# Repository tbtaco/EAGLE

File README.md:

This repository is for any custom PCBs I make that aren't directly part of another project.

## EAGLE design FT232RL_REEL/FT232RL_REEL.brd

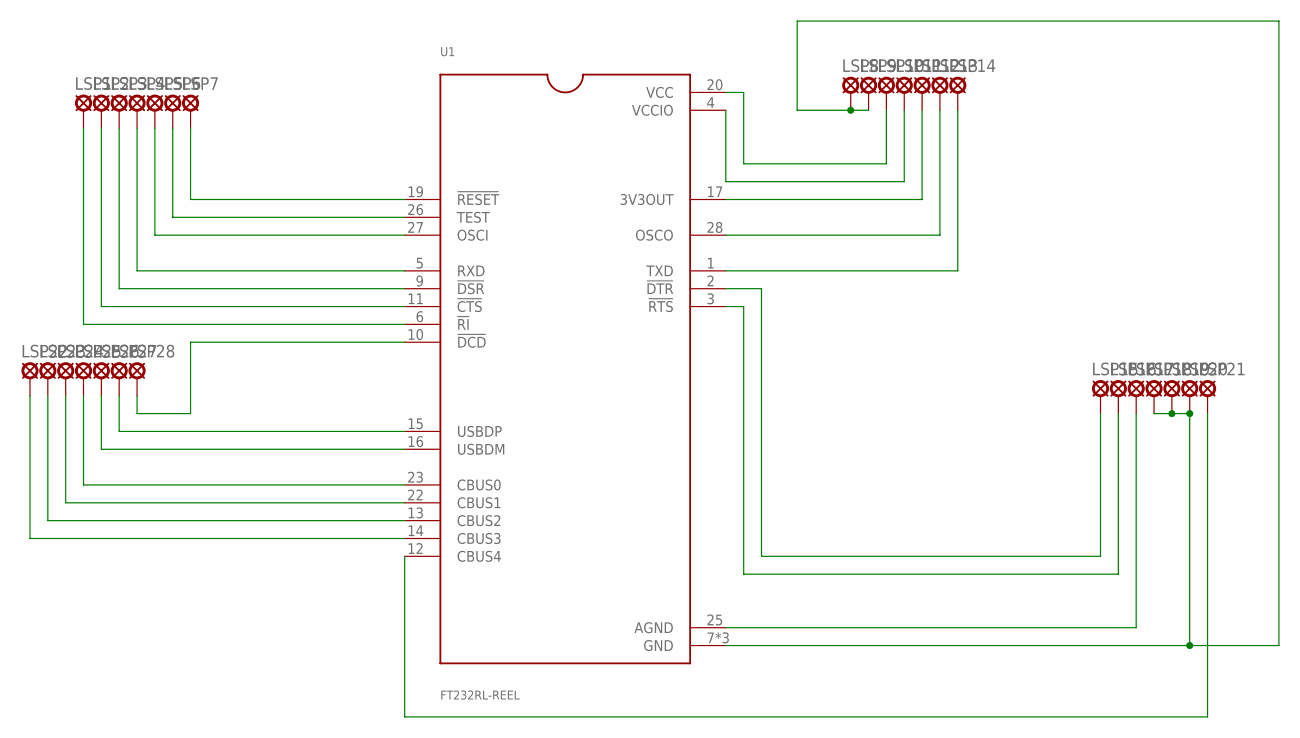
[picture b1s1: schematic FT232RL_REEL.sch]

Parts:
LSP1, LSP2, LSP3, LSP4, LSP5, LSP6, LSP7, LSP8, LSP9, LSP10, LSP11, LSP12, LSP13, LSP14, LSP15, LSP16, LSP17, LSP18, LSP19, LSP20, LSP21, LSP22, LSP23, LSP24, LSP25, LSP26, LSP27, LSP28: LSP10_CLSP10_C; LSP10_C
U1: FT232RL-REEL; SOP65P780X200-28N

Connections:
unnamed: LSP7.P$1, U1.19 (!RESET)
unnamed: LSP6.P$1, U1.26 (TEST)
unnamed: LSP5.P$1, U1.27 (OSCI)
unnamed: LSP4.P$1, U1.5 (RXD)
unnamed: LSP3.P$1, U1.9 (!DSR)
unnamed: LSP2.P$1, U1.11 (!CTS)
unnamed: LSP1.P$1, U1.6 (!RI)
unnamed: LSP28.P$1, U1.10 (!DCD)
unnamed: LSP27.P$1, U1.15 (USBDP)
unnamed: LSP26.P$1, U1.16 (USBDM)
unnamed: LSP25.P$1, U1.23 (CBUS0)
unnamed: LSP24.P$1, U1.22 (CBUS1)
unnamed: LSP23.P$1, U1.13 (CBUS2)
unnamed: LSP22.P$1, U1.14 (CBUS3)
unnamed: LSP21.P$1, U1.12 (CBUS4)
unnamed: LSP8.P$1, LSP9.P$1, LSP18.P$1, LSP19.P$1, LSP20.P$1, U1.7 (GND), U1.18 (GND), U1.21 (GND)
unnamed: LSP17.P$1, U1.25 (AGND)
unnamed: LSP16.P$1, U1.3 (!RTS)
unnamed: LSP15.P$1, U1.2 (!DTR)
unnamed: LSP14.P$1, U1.1 (TXD)
unnamed: LSP13.P$1, U1.28 (OSCO)
unnamed: LSP12.P$1, U1.17 (3V3OUT)
unnamed: LSP11.P$1, U1.4 (VCCIO)
unnamed: LSP10.P$1, U1.20 (VCC)

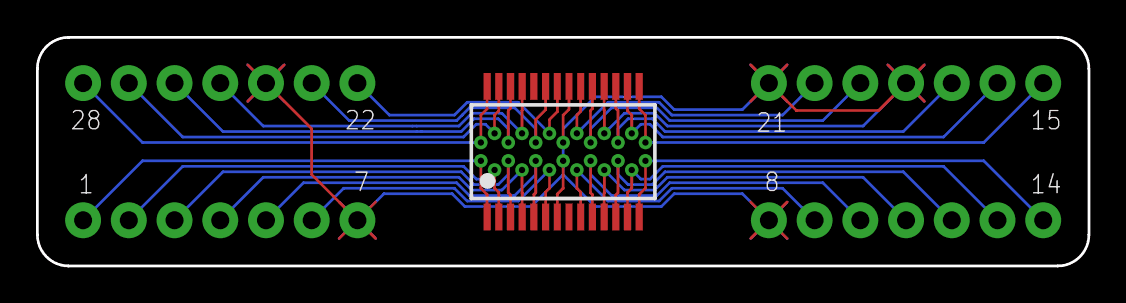
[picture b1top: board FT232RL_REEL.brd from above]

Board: 2 copper layers, 58.4 x 12.7 mm, 29 parts (0 on the bottom side), 24 nets.

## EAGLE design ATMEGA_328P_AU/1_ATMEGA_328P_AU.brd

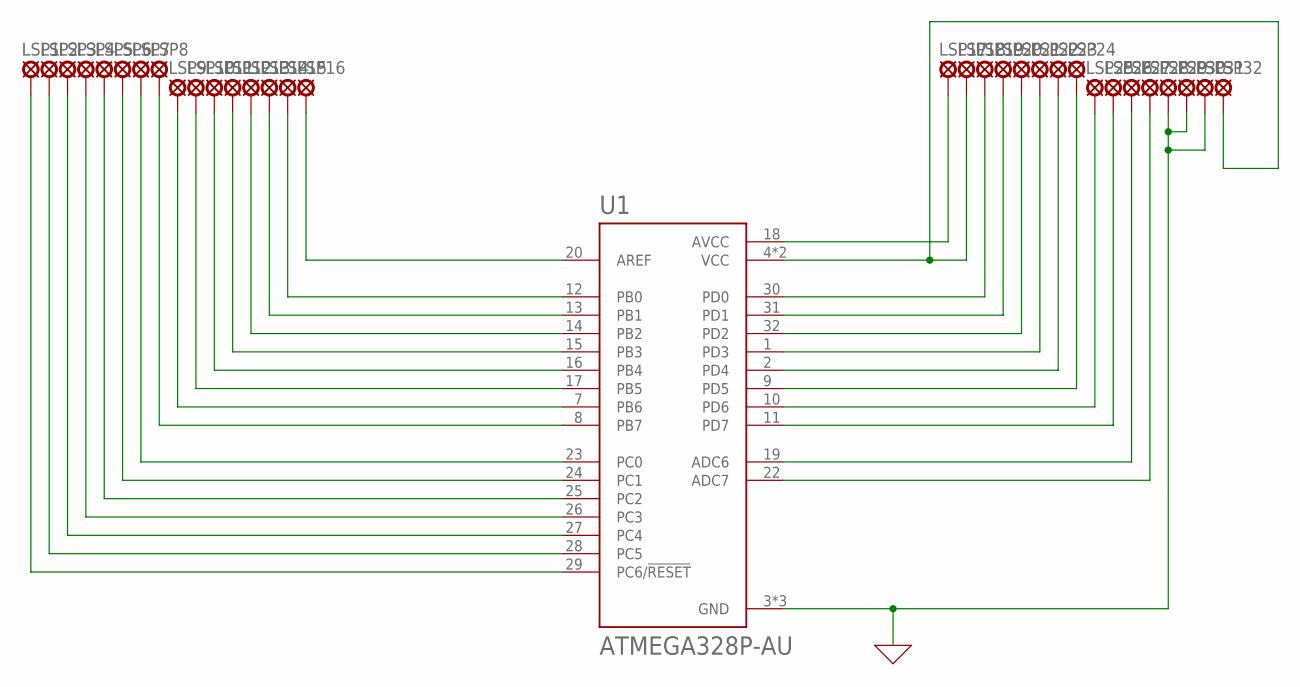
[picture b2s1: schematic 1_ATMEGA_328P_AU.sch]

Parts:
LSP1, LSP2, LSP3, LSP4, LSP5, LSP6, LSP7, LSP8, LSP9, LSP10, LSP11, LSP12, LSP13, LSP14, LSP15, LSP16, LSP17, LSP18, LSP19, LSP20, LSP21, LSP22, LSP23, LSP24, LSP25, LSP26, LSP27, LSP28, LSP29, LSP30, LSP31, LSP32: LSP10_CLSP10_C; LSP10_C
U1: ATMEGA328P-AU; QFP80P900X900X120-32N

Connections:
0: LSP29.P$1, LSP30.P$1, LSP31.P$1, U1.3 (GND), U1.5 (GND), U1.21 (GND)
unnamed: LSP1.P$1, U1.29 (PC6/!RESET)
unnamed: LSP2.P$1, U1.28 (PC5)
unnamed: LSP3.P$1, U1.27 (PC4)
unnamed: LSP4.P$1, U1.26 (PC3)
unnamed: LSP5.P$1, U1.25 (PC2)
unnamed: LSP6.P$1, U1.24 (PC1)
unnamed: LSP7.P$1, U1.23 (PC0)
unnamed: LSP8.P$1, U1.8 (PB7)
unnamed: LSP9.P$1, U1.7 (PB6)
unnamed: LSP10.P$1, U1.17 (PB5)
unnamed: LSP11.P$1, U1.16 (PB4)
unnamed: LSP12.P$1, U1.15 (PB3)
unnamed: LSP13.P$1, U1.14 (PB2)
unnamed: LSP14.P$1, U1.13 (PB1)
unnamed: LSP15.P$1, U1.12 (PB0)
unnamed: LSP16.P$1, U1.20 (AREF)
unnamed: LSP17.P$1, U1.18 (AVCC)
unnamed: LSP18.P$1, LSP32.P$1, U1.4 (VCC), U1.6 (VCC)
unnamed: LSP19.P$1, U1.30 (PD0)
unnamed: LSP20.P$1, U1.31 (PD1)
unnamed: LSP21.P$1, U1.32 (PD2)
unnamed: LSP22.P$1, U1.1 (PD3)
unnamed: LSP23.P$1, U1.2 (PD4)
unnamed: LSP24.P$1, U1.9 (PD5)
unnamed: LSP25.P$1, U1.10 (PD6)
unnamed: LSP26.P$1, U1.11 (PD7)
unnamed: LSP27.P$1, U1.19 (ADC6)
unnamed: LSP28.P$1, U1.22 (ADC7)

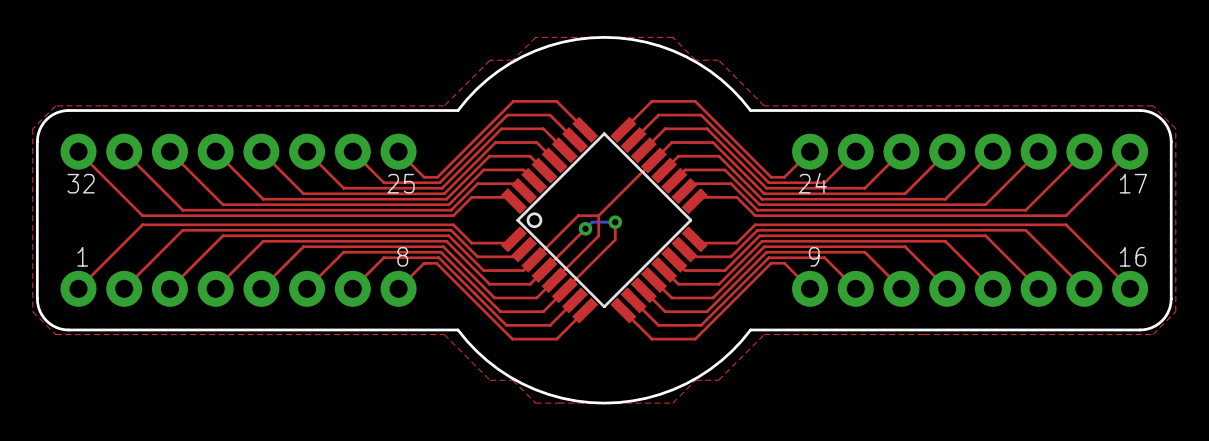
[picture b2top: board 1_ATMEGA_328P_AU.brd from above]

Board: 2 copper layers, 63.0 x 20.3 mm, 33 parts (0 on the bottom side), 29 nets.

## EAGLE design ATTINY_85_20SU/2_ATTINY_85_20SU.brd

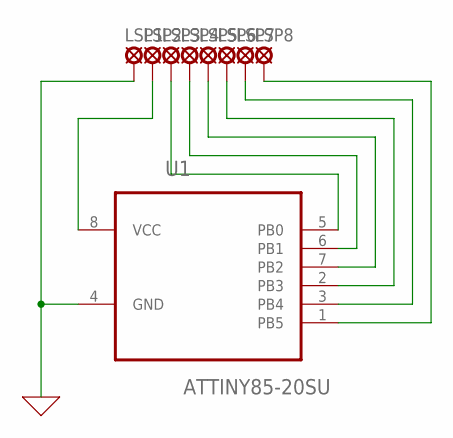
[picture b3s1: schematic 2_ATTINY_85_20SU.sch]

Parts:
LSP1, LSP2, LSP3, LSP4, LSP5, LSP6, LSP7, LSP8: LSP10_CLSP10_C; LSP10_C
U1: ATTINY85-20SU; SOIC127P798X216-8N

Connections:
0: LSP1.P$1, U1.4 (GND)
unnamed: LSP2.P$1, U1.8 (VCC)
unnamed: LSP3.P$1, U1.5 (PB0)
unnamed: LSP4.P$1, U1.6 (PB1)
unnamed: LSP5.P$1, U1.7 (PB2)
unnamed: LSP6.P$1, U1.2 (PB3)
unnamed: LSP7.P$1, U1.3 (PB4)
unnamed: LSP8.P$1, U1.1 (PB5)

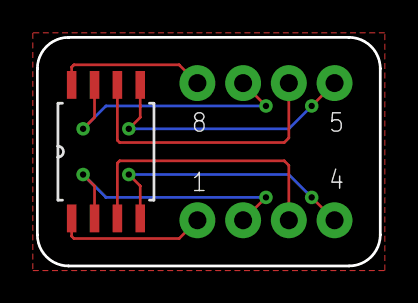
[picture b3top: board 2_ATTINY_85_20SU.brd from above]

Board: 2 copper layers, 19.1 x 12.7 mm, 9 parts (0 on the bottom side), 8 nets.
